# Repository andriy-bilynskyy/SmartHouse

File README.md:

# Water leaks motinoring system

## System overview

## Features
* Easy integration: The system can be easy integrated into existing environment, no additional wires and pipes replacements.
* Flexible configuration: The system can support different count of water leak sensors, it's easy to add or remove water leak sensor during runtime operation.
* User friendly interface: The system is using simple web interface for configuration and monitoring.
* Non-volatile operation: The system can work without electricity due to backup power supply.
* Low power consumption: Due to used technologies the system use low electricity
* No high voltage: All system components are working with safe 12 volts power supply.
* New technologies: BLE sensors, WI-FI access, WEB user interface.

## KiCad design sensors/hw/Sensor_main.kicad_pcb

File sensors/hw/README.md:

[PCB manufacture](https://www.elecrow.com/10pcs-2-layer-pcb.html)

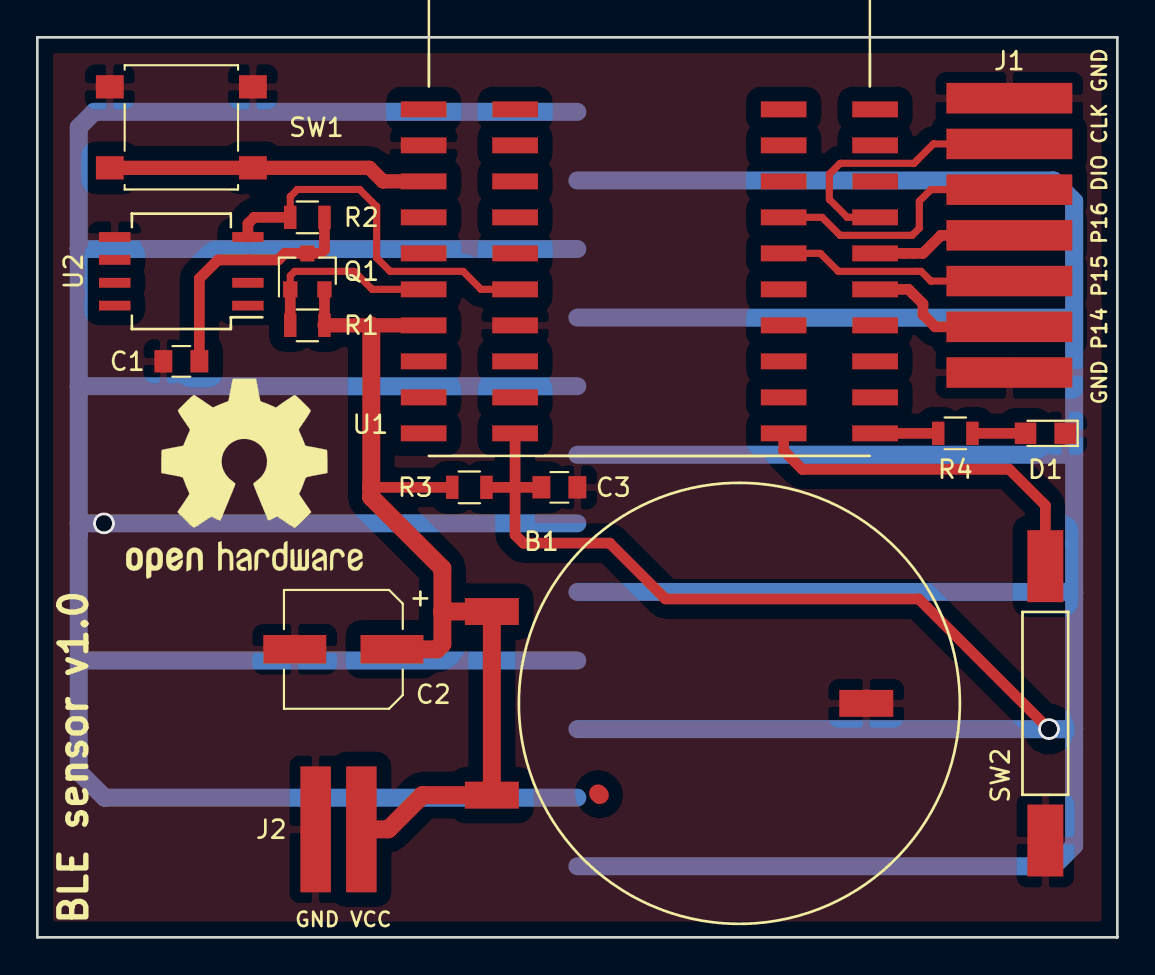
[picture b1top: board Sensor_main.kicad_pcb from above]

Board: 2 copper layers, 60.0 x 50.0 mm, 17 parts (1 on the bottom side), 15 nets.

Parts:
B1: CR2477
C1: 100n; C_0805
C2: 220u (RC)6,3*7,7; CP_Elec_6.3x7.7
C3: 10n; C_0805
D1: FYLS-0805GD; LED_0805
J1: ZL211-07KG; ZL211-07G
J2: ZL211-02KG; ZL201-02G
Q1: IRLML6401; SOT-23
R1: 47K; R_0805
R2: 4.7K; R_0805
R3: 2M; R_0805
R4: 270R; R_0805
SW1: B3FS-1000P; SW_SPST_B3S-1000
SW2: KA-80
U1: NRF51822_Eval
U2: DS18B20; SO-8_5.3x6.2mm_Pitch1.27mm
U3: WATER_SENSOR

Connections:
/1WIRE: R2.2, U1.10, U2.4
/AIN: C3.1, R3.2, U1.18, U3.1
/CLK: J1.2, U1.32
/DIO: J1.3, U1.31
/P14: J1.6, U1.28
/P15: J1.5, U1.29
/P16: J1.4, U1.30
/PON#: Q1.1, R1.2, U1.9
GND: B1.2, C1.2, C2.2, C3.2, D1.1, J1.1, J1.7, J2.2, SW1.1, SW2.2, U1.1, U1.12, U2.5, U3.2
unnamed: C1.1, Q1.3, R2.1, U2.3
unnamed: D1.2, R4.1
unnamed: R4.2, U1.20
unnamed: SW1.2, U1.3
unnamed: SW2.1, U1.19
VCC: B1.1, C2.1, J2.1, Q1.2, R1.1, R3.1, U1.11

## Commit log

2018-01-25 Initial commit.
2018-01-25 Fixed toochain path.
2018-01-25 Fixed sensor timediff.
2018-02-03 Fixed SQL request. (subscribe waterleak sensor)
2018-02-04 Fixed log units.
2018-03-17 Updated service scripts. Fixed make for target.
2018-03-17 Fixed make for target.
2018-03-17 Fixed startup scripts.
2018-03-17 Fixed startup script.
2018-05-23 DB fixes
